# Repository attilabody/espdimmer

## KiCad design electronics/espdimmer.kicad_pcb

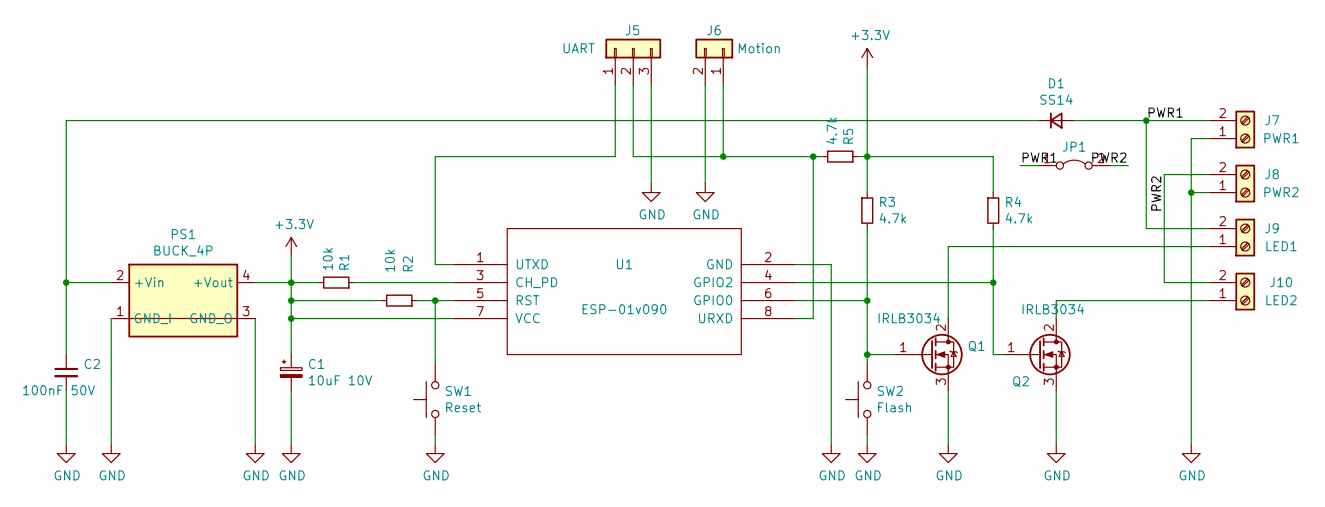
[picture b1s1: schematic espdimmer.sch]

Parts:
C1: 10uF 10V; CP_EIA-3216-10_Kemet-I_Pad1.58x1.35mm_HandSolder
C2: 100nF 50V; C_0805_2012Metric_Pad1.15x1.40mm_HandSolder
D1: SS14; D_SMA_Handsoldering
J5: UART; PinHeader_1x03_P2.54mm_Vertical
J6: Motion; PinHeader_1x02_P2.54mm_Vertical
J7: PWR1; TerminalBlock_bornier-2_P5.08mm
J8: PWR2; TerminalBlock_bornier-2_P5.08mm
J9: LED1; TerminalBlock_bornier-2_P5.08mm
J10: LED2; TerminalBlock_bornier-2_P5.08mm
JP1: Jumper_2_Bridged; SolderJumper-2_P1.3mm_Open_TrianglePad1.0x1.5mm
PS1: BUCK_4P; XM1584_buck_mod_4p
Q1, Q2: IRLB3034; TO-220-3_Vertical
R1, R2: 10k; R_0805_2012Metric_Pad1.15x1.40mm_HandSolder
R3, R4, R5: 4.7k; R_0805_2012Metric_Pad1.15x1.40mm_HandSolder
SW1: Reset; SW_PUSH_6mm
SW2: Flash; SW_PUSH_6mm
U1: ESP-01v090; ESP-01

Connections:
+3V3: C1.1, PS1.4 (+Vout), R1.2, R2.2, R3.1, R4.1, R5.1, U1.7 (VCC)
/PWR1: D1.2 (A), J7.2, J9.2, JP1.1 (A)
/PWR2: J8.2, J10.2, JP1.2 (B)
GND: C1.2, C2.2, J5.3, J6.2, J7.1, J8.1, PS1.1 (GND_I), PS1.3 (GND_O), Q1.3 (S), Q2.3 (S), SW1.2, SW2.2, U1.2 (GND)
unnamed: C2.1, D1.1 (K), PS1.2 (+Vin)
unnamed: J5.1, U1.1 (UTXD)
unnamed: J5.2, J6.1, R5.2, U1.8 (URXD)
unnamed: J9.1, Q1.2 (D)
unnamed: J10.1, Q2.2 (D)
unnamed: Q1.1 (G), R3.2, SW2.1, U1.6 (GPIO0)
unnamed: Q2.1 (G), R4.2, U1.4 (GPIO2)
unnamed: R1.1, U1.3 (CH_PD)
unnamed: R2.1, SW1.1, U1.5 (RST)

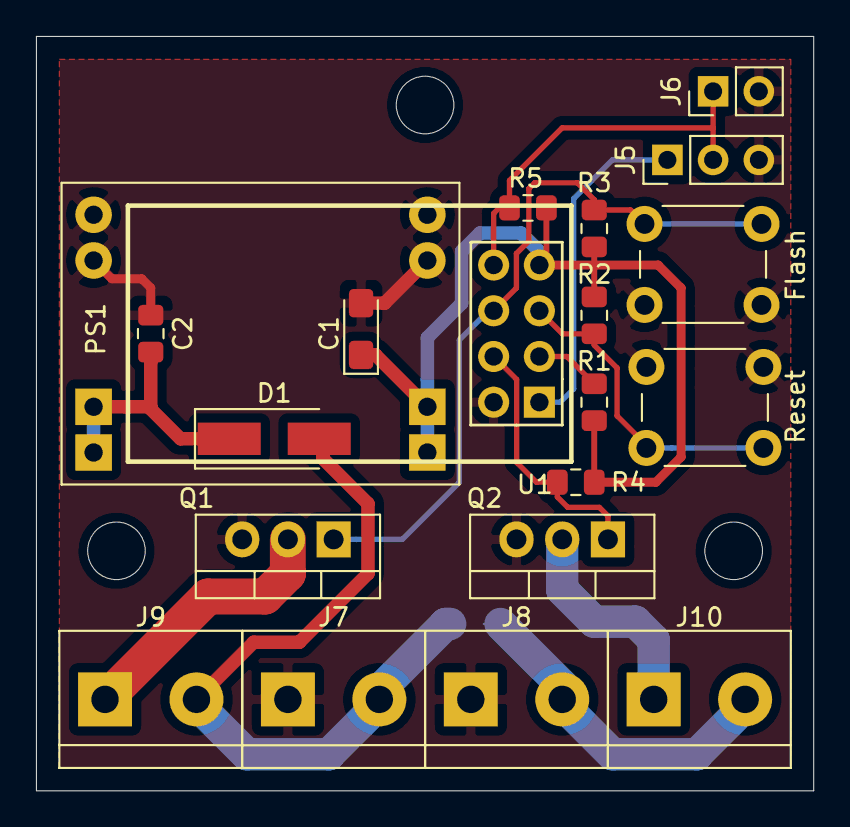
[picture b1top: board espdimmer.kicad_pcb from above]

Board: 2 copper layers, 43.2 x 41.9 mm, 21 parts (1 on the bottom side), 13 nets.

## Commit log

2021-01-04 reading SSID and password from config file
2021-01-05 MQTT client proto
2021-01-07 MQTT robustness
2021-01-10 PCB V1 (narrow)
2021-01-19 Schematics and PCB design updated
2021-01-22 Schematics/PCB updated
2021-05-13 esphome config added
2021-05-13 git subrepo clone (merge) https://github.com/jdunmire/kicad-ESP8266.git electronics/esp8266
    subrepo:
    subdir: "electronics/esp8266"
    merged: "1f3d2c6"
    upstream:
    origin: "https://github.com/jdunmire/kicad-ESP8266.git"
    branch: "master"
2021-05-13 switched to internal esp8266 libs
2021-06-22 Housing added
